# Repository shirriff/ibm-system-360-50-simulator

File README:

Microcode in 2050_vol18/19/20_Sep72.pdf

Volume 20 QZ_000_1 etc has mapping from address to e.g. QT100 page.

Microcode overview in Z22-2833-R_2050_Processing_Unit_Field_Engineering_Diagram_Manual_Jul66.pdf
Page 14 has instruction table

Warning: edit .ts files not .js!

Compile typescript with "tsc"

start web server:
python3 -m http.server

Open tests in browser, e.g. tests/instructions.html
Tests don't all pass currently

decode.js: generates the microcode expression box
disasm.js: disassembles a System/360 instruction
engine.js: the actual simulator engine
io.js: i/O simulation: very basic
sim.js: top-level simulator
utils.js: shared utility functions
viewer.js: used by display.html and viewer.html

display.html: displays microcode
sim.html: main simulator
viewer.html: search/diff

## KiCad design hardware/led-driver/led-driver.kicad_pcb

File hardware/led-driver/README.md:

This is a driver board for the Model 50 console lights (under development).
This board has 18 LEDs, matching the two-byte display segment on the console.
It would take 15 boards for the whole console, which has approximately 271 LEDs.
I'm planning to use yellow/orange 590nm LEDs which is what the [IBM 1620 Jr](https://github.com/IBM-1620/Junior) project used after a bunch of testing to see what matched the bulbs most closely.

The board uses [PCA9634](https://www.nxp.com/docs/en/data-sheet/PCA9634.pdf) LED I2C PWM driver chips.
Each chip drives 8 LEDs, so each board has three chips. The extra 6 LED outputs are wired and can be connected to other console LEDs.
This supports the irregular console lights that don't fit into groups of 18.

The LED chips have I2C addresses *001bbbb*,
*011bbbb*, and *101bbbb* where *bbbb* are the board bits from the solder jumpers. The first two bits select the chip on the board (0, 1, 2).
The first chip handles the low-order byte, the second chip handles the high-order byte, and the third chip handles the two parity lights.

The board has some optional functionality that can be installed as needed.

A [PCA9555](https://www.nxp.com/docs/en/data-sheet/PCA9555.pdf) 16-bit GPIO can read 16 switches from the console.
Its I2C address is *0100bbb*.

A [MCP47CVB01](https://ww1.microchip.com/downloads/en/DeviceDoc/MCP47CXBXX-Data-Sheet-DS20006089B.pdf) DAC chip provides a current to drive the console meter. Its I2C address is *10010bb*.

Two [ADS7828EB](https://www.ti.com/lit/gpn/ads7828) provide 8-channel analog-to-digital conversion.
This can read the console potentiometers.
The I2C addresses are *100100b* and *100101b*, using a single board bit. The second-last bit selects the chip on the board.

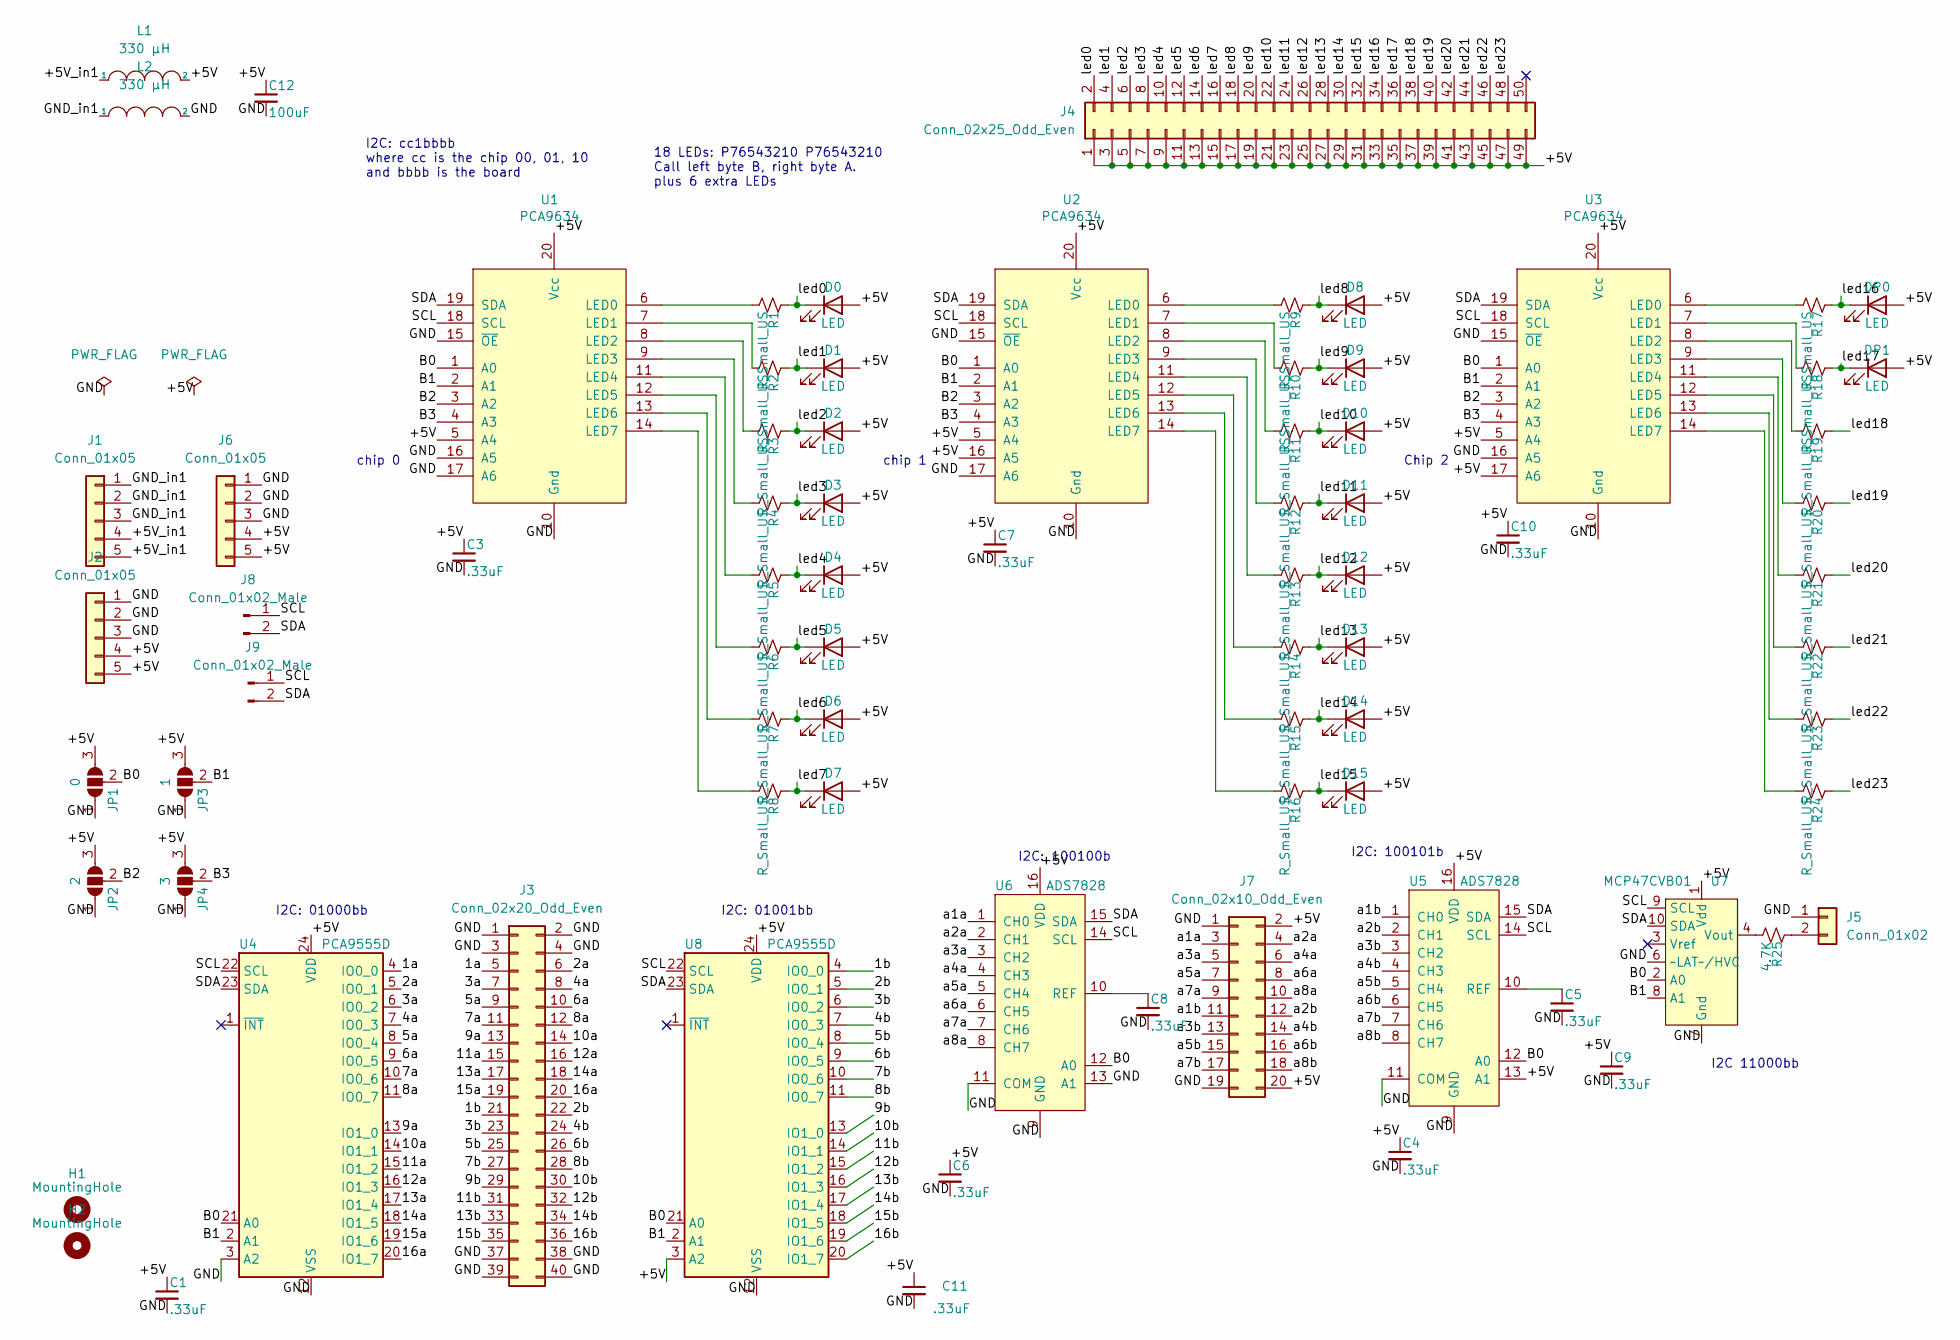
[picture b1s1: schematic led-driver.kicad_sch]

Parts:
C1, C3, C4, C5, C6, C7, C8, C9, C10, C11: .33uF; C_0805_2012Metric_Pad1.18x1.45mm_HandSolder
C12: 100uF; CP_EIA-7343-40_Kemet-Y_Pad2.25x2.55mm_HandSolder
D0, D1, D2, D3, D4, D5, D6, D7, D8, D9, D10, D11, D12, D13, D14, D15: LED; LED_D3.0mm-nosilk
DP0, DP1: LED; LED_D3.0mm-nosilk
H1, H2: MountingHole; MountingHole_3.7mm
J1, J2, J6: Conn_01x05; SAMTEC_TSS-105-04-F-S-RA
J3: Conn_02x20_Odd_Even; SAMTEC_TSS-120-04-F-D-RA-mirror
J4: Conn_02x25_Odd_Even; SAMTEC_TSS-125-04-F-D-RA-mirror
J5: Conn_01x02; SAMTEC_TSS-102-04-F-S-RA
J7: Conn_02x10_Odd_Even; SAMTEC_TSS-110-04-F-D-RA-mirror
J8, J9: Conn_01x02_Male; SAMTEC_TSS-102-04-F-S-RA
JP1: 0; SolderJumper-3_P1.3mm_Open_RoundedPad1.0x1.5mm_NumberLabels
JP2: 2; SolderJumper-3_P1.3mm_Open_RoundedPad1.0x1.5mm_NumberLabels
JP3: 1; SolderJumper-3_P1.3mm_Open_RoundedPad1.0x1.5mm_NumberLabels
JP4: 3; SolderJumper-3_P1.3mm_Open_RoundedPad1.0x1.5mm_NumberLabels
L1, L2: 330 µH; L_Bourns_SDR1307
R1, R2, R3, R4, R5, R6, R7, R8, R9, R10, R11, R12, R13, R14, R15, R16, R17, R18, R19, R20, R21, R22, R23, R24: R_Small_US; R_0805_2012Metric_Pad1.20x1.40mm_HandSolder
R25: 4.7K; R_0805_2012Metric_Pad1.20x1.40mm_HandSolder
U1, U2, U3: PCA9634; SOIC-20W_7.5x12.8mm_P1.27mm
U4, U8: PCA9555D; SOIC-24W_7.5x15.4mm_P1.27mm
U5, U6: ADS7828; TSSOP-16_4.4x5mm_P0.65mm
U7: MCP47CVB01; MSOP-10_3x3mm_P0.5mm

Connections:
/1a: J3.5, U4.4 (IO0_0)
/1b: J3.21, U8.4 (IO0_0)
/2a: J3.6, U4.5 (IO0_1)
/2b: J3.22, U8.5 (IO0_1)
/3a: J3.7, U4.6 (IO0_2)
/3b: J3.23, U8.6 (IO0_2)
/4a: J3.8, U4.7 (IO0_3)
/4b: J3.24, U8.7 (IO0_3)
/5a: J3.9, U4.8 (IO0_4)
/5b: J3.25, U8.8 (IO0_4)
/6a: J3.10, U4.9 (IO0_5)
/6b: J3.26, U8.9 (IO0_5)
/7a: J3.11, U4.10 (IO0_6)
/7b: J3.27, U8.10 (IO0_6)
/8a: J3.12, U4.11 (IO0_7)
/8b: J3.28, U8.11 (IO0_7)
/9a: J3.13, U4.13 (IO1_0)
/9b: J3.29, U8.13 (IO1_0)
/10a: J3.14, U4.14 (IO1_1)
/10b: J3.30, U8.14 (IO1_1)
/11a: J3.15, U4.15 (IO1_2)
/11b: J3.31, U8.15 (IO1_2)
/12a: J3.16, U4.16 (IO1_3)
/12b: J3.32, U8.16 (IO1_3)
/13a: J3.17, U4.17 (IO1_4)
/13b: J3.33, U8.17 (IO1_4)
/14a: J3.18, U4.18 (IO1_5)
/14b: J3.34, U8.18 (IO1_5)
/15a: J3.19, U4.19 (IO1_6)
/15b: J3.35, U8.19 (IO1_6)
/16a: J3.20, U4.20 (IO1_7)
/16b: J3.36, U8.20 (IO1_7)
/+5V: C1.1, C3.1, C4.1, C6.1, C7.1, C9.1, C10.1, C11.1, C12.1, D0.2 (A), D1.2 (A), D2.2 (A), D3.2 (A), D4.2 (A), D5.2 (A), D6.2 (A), D7.2 (A), D8.2 (A), D9.2 (A), D10.2 (A), D11.2 (A), D12.2 (A), D13.2 (A), D14.2 (A), D15.2 (A), DP0.2 (A), DP1.2 (A), J2.4, J2.5, J4.1, J4.3, J4.5, J4.7, J4.9, J4.11, J4.13, J4.15, J4.17, J4.19, J4.21, J4.23, J4.25, J4.27, J4.29, J4.31, J4.33, J4.35, J4.37, J4.39, J4.41, J4.43, J4.45, J4.47, J4.49, J6.4, J6.5, J7.2, J7.20, JP1.3 (B), JP2.3 (B), JP3.3 (B), JP4.3 (B), L1.2, U1.5 (A4), U1.20 (Vcc), U2.5 (A4), U2.16 (A5), U2.20 (Vcc), U3.5 (A4), U3.17 (A6), U3.20 (Vcc), U4.24 (VDD), U5.13 (A1), U5.16 (VDD), U6.16 (VDD), U7.1 (Vdd), U8.3 (A2), U8.24 (VDD)
/+5V_in1: J1.4, J1.5, L1.1
/B0: JP1.2 (C), U1.1 (A0), U2.1 (A0), U3.1 (A0), U4.21 (A0), U5.12 (A0), U6.12 (A0), U7.2 (A0), U8.21 (A0)
/B1: JP3.2 (C), U1.2 (A1), U2.2 (A1), U3.2 (A1), U4.2 (A1), U7.8 (A1), U8.2 (A1)
/B2: JP2.2 (C), U1.3 (A2), U2.3 (A2), U3.3 (A2)
/B3: JP4.2 (C), U1.4 (A3), U2.4 (A3), U3.4 (A3)
/GND: C1.2, C3.2, C4.2, C5.2, C6.2, C7.2, C8.2, C9.2, C10.2, C11.2, C12.2, J2.1, J2.2, J2.3, J3.1, J3.2, J3.3, J3.4, J3.37, J3.38, J3.39, J3.40, J5.1, J6.1, J6.2, J6.3, J7.1, J7.19, JP1.1 (A), JP2.1 (A), JP3.1 (A), JP4.1 (A), L2.2, U1.10 (Gnd), U1.15 (~OE), U1.16 (A5), U1.17 (A6), U2.10 (Gnd), U2.15 (~OE), U2.17 (A6), U3.10 (Gnd), U3.15 (~OE), U3.16 (A5), U4.3 (A2), U4.12 (VSS), U5.9 (GND), U5.11 (COM), U6.9 (GND), U6.11 (COM), U6.13 (A1), U7.6 (~LAT~/HVC), U7.7 (Gnd), U8.12 (VSS)
/GND_in1: J1.1, J1.2, J1.3, L2.1
/SCL: J8.1, J9.1, U1.18 (SCL), U2.18 (SCL), U3.18 (SCL), U4.22 (SCL), U5.14 (SCL), U6.14 (SCL), U7.9 (SCL), U8.22 (SCL)
/SDA: J8.2, J9.2, U1.19 (SDA), U2.19 (SDA), U3.19 (SDA), U4.23 (SDA), U5.15 (SDA), U6.15 (SDA), U7.10 (SDA), U8.23 (SDA)
/a1a: J7.3, U6.1 (CH0)
/a1b: J7.11, U5.1 (CH0)
/a2a: J7.4, U6.2 (CH1)
/a2b: J7.12, U5.2 (CH1)
/a3a: J7.5, U6.3 (CH2)
/a3b: J7.13, U5.3 (CH2)
/a4a: J7.6, U6.4 (CH3)
/a4b: J7.14, U5.4 (CH3)
/a5a: J7.7, U6.5 (CH4)
/a5b: J7.15, U5.5 (CH4)
/a6a: J7.8, U6.6 (CH5)
/a6b: J7.16, U5.6 (CH5)
/a7a: J7.9, U6.7 (CH6)
/a7b: J7.17, U5.7 (CH6)
/a8a: J7.10, U6.8 (CH7)
/a8b: J7.18, U5.8 (CH7)
/led0: D0.1 (K), J4.2, R1.1
/led1: D1.1 (K), J4.4, R2.1
/led2: D2.1 (K), J4.6, R3.1
/led3: D3.1 (K), J4.8, R4.1
/led4: D4.1 (K), J4.10, R5.1
/led5: D5.1 (K), J4.12, R6.1
/led6: D6.1 (K), J4.14, R7.1
/led7: D7.1 (K), J4.16, R8.1
/led8: D8.1 (K), J4.18, R9.1
/led9: D9.1 (K), J4.20, R10.1
/led10: D10.1 (K), J4.22, R11.1
/led11: D11.1 (K), J4.24, R12.1
/led12: D12.1 (K), J4.26, R13.1
/led13: D13.1 (K), J4.28, R14.1
/led14: D14.1 (K), J4.30, R15.1
/led15: D15.1 (K), J4.32, R16.1
/led16: DP0.1 (K), J4.34, R17.1
/led17: DP1.1 (K), J4.36, R18.1
/led18: J4.38, R19.1
/led19: J4.40, R20.1
/led20: J4.42, R21.1
/led21: J4.44, R22.1
/led22: J4.46, R23.1
/led23: J4.48, R24.1
unnamed: C5.1, U5.10 (REF)
unnamed: C8.1, U6.10 (REF)
unnamed: J5.2, R25.1
unnamed: R1.2, U1.6 (LED0)
unnamed: R2.2, U1.7 (LED1)
unnamed: R3.2, U1.8 (LED2)
unnamed: R4.2, U1.9 (LED3)
unnamed: R5.2, U1.11 (LED4)
unnamed: R6.2, U1.12 (LED5)
unnamed: R7.2, U1.13 (LED6)
unnamed: R8.2, U1.14 (LED7)
unnamed: R9.2, U2.6 (LED0)
unnamed: R10.2, U2.7 (LED1)
unnamed: R11.2, U2.8 (LED2)
unnamed: R12.2, U2.9 (LED3)
unnamed: R13.2, U2.11 (LED4)
unnamed: R14.2, U2.12 (LED5)
unnamed: R15.2, U2.13 (LED6)
unnamed: R16.2, U2.14 (LED7)
unnamed: R17.2, U3.6 (LED0)
unnamed: R18.2, U3.7 (LED1)
unnamed: R19.2, U3.8 (LED2)
unnamed: R20.2, U3.9 (LED3)
unnamed: R21.2, U3.11 (LED4)
unnamed: R22.2, U3.12 (LED5)
unnamed: R23.2, U3.13 (LED6)
unnamed: R24.2, U3.14 (LED7)
unnamed: R25.2, U7.4 (Vout)

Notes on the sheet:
I2C: 100101b
chip 1
I2C 11000bb
I2C: cc1bbbb where cc is the chip 00, 01, 10 and bbbb is the board
Chip 2
chip 0
18 LEDs: P76543210 P76543210 Call left byte B, right byte A. plus 6 extra LEDs
I2C: 01000bb
I2C: 100100b
I2C: 01001bb

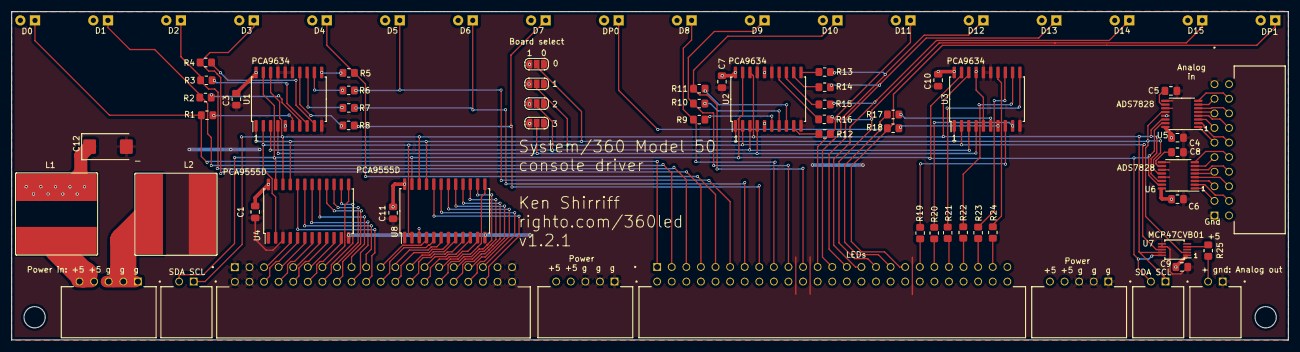
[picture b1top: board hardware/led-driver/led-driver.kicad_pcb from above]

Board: 2 copper layers, 222.2 x 57.1 mm, 79 parts (0 on the bottom side), 110 nets.

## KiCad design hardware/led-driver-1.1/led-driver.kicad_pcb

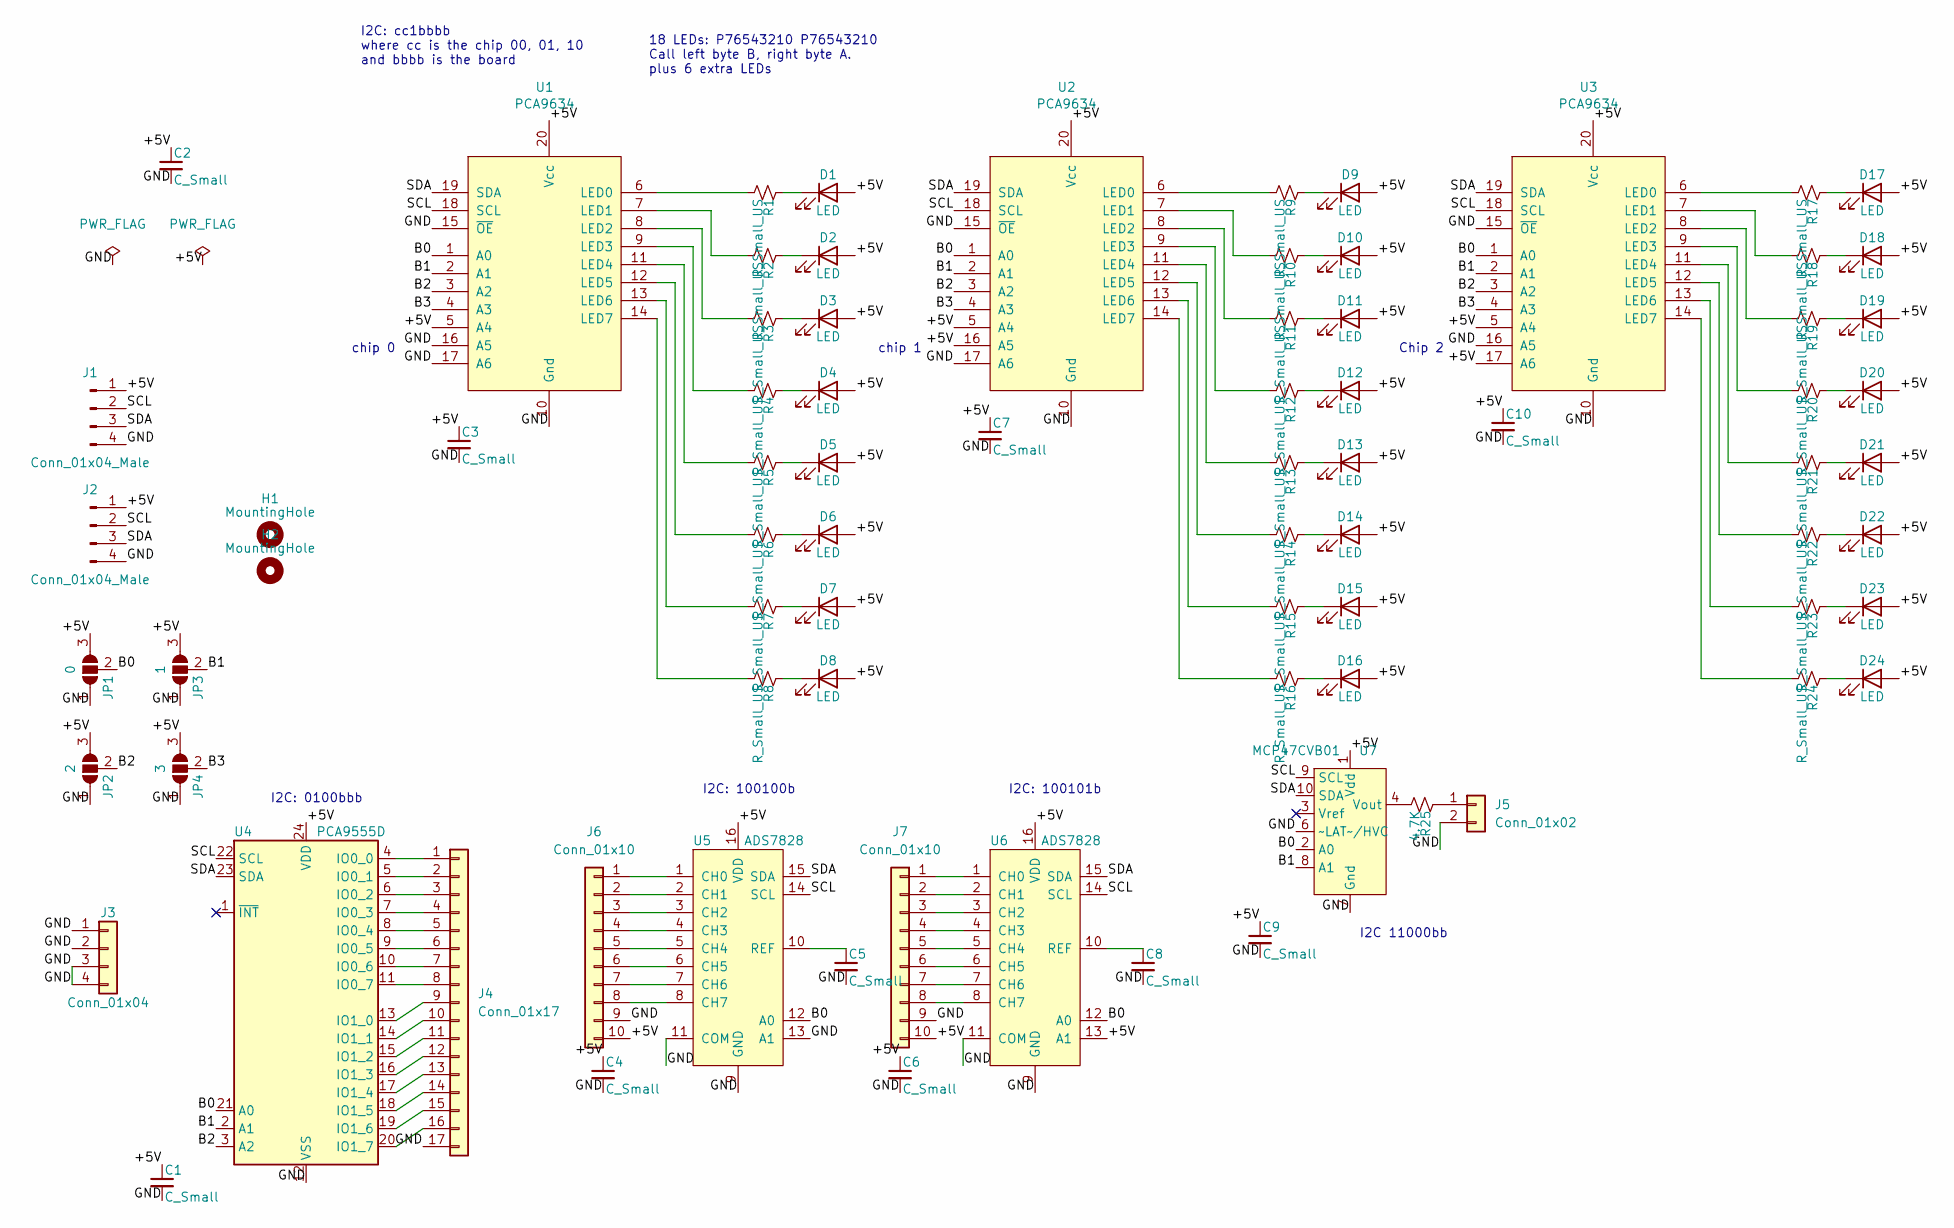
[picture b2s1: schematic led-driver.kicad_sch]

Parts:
C1, C2, C3, C4, C5, C6, C7, C8, C9, C10: C_Small; C_0805_2012Metric_Pad1.18x1.45mm_HandSolder
D1, D2, D3, D4, D5, D6, D7, D8, D9, D10, D11, D12, D13, D14, D15, D16, D17, D18: LED; LED_D3.0mm-nosilk
D19, D20, D21, D22, D23, D24: LED; PinHeader_1x02_P2.54mm_Vertical
H1, H2: MountingHole; MountingHole_3.7mm
J1, J2: Conn_01x04_Male; PinHeader_1x04_P2.54mm_Vertical_mirrored
J3: Conn_01x04; PinSocket_1x04_P2.54mm_Vertical
J4: Conn_01x17; PinSocket_1x17_P2.54mm_Vertical
J5: Conn_01x02; PinHeader_1x02_P2.54mm_Vertical
J6, J7: Conn_01x10; PinHeader_1x10_P2.54mm_Vertical
JP1: 0; SolderJumper-3_P1.3mm_Open_RoundedPad1.0x1.5mm_NumberLabels
JP2: 2; SolderJumper-3_P1.3mm_Open_RoundedPad1.0x1.5mm_NumberLabels
JP3: 1; SolderJumper-3_P1.3mm_Open_RoundedPad1.0x1.5mm_NumberLabels
JP4: 3; SolderJumper-3_P1.3mm_Open_RoundedPad1.0x1.5mm_NumberLabels
R1, R2, R3, R4, R5, R6, R7, R8, R9, R10, R11, R12, R13, R14, R15, R16, R17, R18, R19, R20, R21, R22, R23, R24: R_Small_US; R_0805_2012Metric_Pad1.20x1.40mm_HandSolder
R25: 4.7K; R_0805_2012Metric_Pad1.20x1.40mm_HandSolder
U1, U2, U3: PCA9634; SOIC-20W_7.5x12.8mm_P1.27mm
U4: PCA9555D; SOIC-24W_7.5x15.4mm_P1.27mm
U5, U6: ADS7828; TSSOP-16_4.4x5mm_P0.65mm
U7: MCP47CVB01; MSOP-10_3x3mm_P0.5mm

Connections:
/+5V: C1.1, C2.1, C3.1, C4.1, C6.1, C7.1, C9.1, C10.1, D1.2 (A), D2.2 (A), D3.2 (A), D4.2 (A), D5.2 (A), D6.2 (A), D7.2 (A), D8.2 (A), D9.2 (A), D10.2 (A), D11.2 (A), D12.2 (A), D13.2 (A), D14.2 (A), D15.2 (A), D16.2 (A), D17.2 (A), D18.2 (A), D19.2 (A), D20.2 (A), D21.2 (A), D22.2 (A), D23.2 (A), D24.2 (A), J1.1, J2.1, J6.10, J7.10, JP1.3 (B), JP2.3 (B), JP3.3 (B), JP4.3 (B), U1.5 (A4), U1.20 (Vcc), U2.5 (A4), U2.16 (A5), U2.20 (Vcc), U3.5 (A4), U3.17 (A6), U3.20 (Vcc), U4.24 (VDD), U5.16 (VDD), U6.13 (A1), U6.16 (VDD), U7.1 (Vdd)
/B0: JP1.2 (C), U1.1 (A0), U2.1 (A0), U3.1 (A0), U4.21 (A0), U5.12 (A0), U6.12 (A0), U7.2 (A0)
/B1: JP3.2 (C), U1.2 (A1), U2.2 (A1), U3.2 (A1), U4.2 (A1), U7.8 (A1)
/B2: JP2.2 (C), U1.3 (A2), U2.3 (A2), U3.3 (A2), U4.3 (A2)
/B3: JP4.2 (C), U1.4 (A3), U2.4 (A3), U3.4 (A3)
/GND: C1.2, C2.2, C3.2, C4.2, C5.2, C6.2, C7.2, C8.2, C9.2, C10.2, J1.4, J2.4, J3.1, J3.2, J3.3, J3.4, J4.17, J5.2, J6.9, J7.9, JP1.1 (A), JP2.1 (A), JP3.1 (A), JP4.1 (A), U1.10 (Gnd), U1.15 (~OE), U1.16 (A5), U1.17 (A6), U2.10 (Gnd), U2.15 (~OE), U2.17 (A6), U3.10 (Gnd), U3.15 (~OE), U3.16 (A5), U4.12 (VSS), U5.9 (GND), U5.11 (COM), U5.13 (A1), U6.9 (GND), U6.11 (COM), U7.6 (~LAT~/HVC), U7.7 (Gnd)
/SCL: J1.2, J2.2, U1.18 (SCL), U2.18 (SCL), U3.18 (SCL), U4.22 (SCL), U5.14 (SCL), U6.14 (SCL), U7.9 (SCL)
/SDA: J1.3, J2.3, U1.19 (SDA), U2.19 (SDA), U3.19 (SDA), U4.23 (SDA), U5.15 (SDA), U6.15 (SDA), U7.10 (SDA)
unnamed: C5.1, U5.10 (REF)
unnamed: C8.1, U6.10 (REF)
unnamed: D1.1 (K), R1.1
unnamed: D2.1 (K), R2.1
unnamed: D3.1 (K), R3.1
unnamed: D4.1 (K), R4.1
unnamed: D5.1 (K), R5.1
unnamed: D6.1 (K), R6.1
unnamed: D7.1 (K), R7.1
unnamed: D8.1 (K), R8.1
unnamed: D9.1 (K), R9.1
unnamed: D10.1 (K), R10.1
unnamed: D11.1 (K), R11.1
unnamed: D12.1 (K), R12.1
unnamed: D13.1 (K), R13.1
unnamed: D14.1 (K), R14.1
unnamed: D15.1 (K), R15.1
unnamed: D16.1 (K), R16.1
unnamed: D17.1 (K), R17.1
unnamed: D18.1 (K), R18.1
unnamed: D19.1 (K), R19.1
unnamed: D20.1 (K), R20.1
unnamed: D21.1 (K), R21.1
unnamed: D22.1 (K), R22.1
unnamed: D23.1 (K), R23.1
unnamed: D24.1 (K), R24.1
unnamed: J5.1, R25.1
unnamed: J6.1, U5.1 (CH0)
unnamed: J6.2, U5.2 (CH1)
unnamed: J6.3, U5.3 (CH2)
unnamed: J6.4, U5.4 (CH3)
unnamed: J6.5, U5.5 (CH4)
unnamed: J6.6, U5.6 (CH5)
unnamed: J6.7, U5.7 (CH6)
unnamed: J6.8, U5.8 (CH7)
unnamed: R1.2, U1.6 (LED0)
unnamed: R2.2, U1.7 (LED1)
unnamed: R3.2, U1.8 (LED2)
unnamed: R4.2, U1.9 (LED3)
unnamed: R5.2, U1.11 (LED4)
unnamed: R6.2, U1.12 (LED5)
unnamed: R7.2, U1.13 (LED6)
unnamed: R8.2, U1.14 (LED7)
unnamed: R9.2, U2.6 (LED0)
unnamed: R10.2, U2.7 (LED1)
unnamed: R11.2, U2.8 (LED2)
unnamed: R12.2, U2.9 (LED3)
unnamed: R13.2, U2.11 (LED4)
unnamed: R14.2, U2.12 (LED5)
unnamed: R15.2, U2.13 (LED6)
unnamed: R16.2, U2.14 (LED7)
unnamed: R17.2, U3.6 (LED0)
unnamed: R18.2, U3.7 (LED1)
unnamed: R19.2, U3.8 (LED2)
unnamed: R20.2, U3.9 (LED3)
unnamed: R21.2, U3.11 (LED4)
unnamed: R22.2, U3.12 (LED5)
unnamed: R23.2, U3.13 (LED6)
unnamed: R24.2, U3.14 (LED7)
unnamed: R25.2, U7.4 (Vout)
unnamed: J4.1, U4.4 (IO0_0)
unnamed: J4.2, U4.5 (IO0_1)
unnamed: J4.3, U4.6 (IO0_2)
unnamed: J4.4, U4.7 (IO0_3)
unnamed: J4.5, U4.8 (IO0_4)
unnamed: J4.6, U4.9 (IO0_5)
unnamed: J4.7, U4.10 (IO0_6)
unnamed: J4.8, U4.11 (IO0_7)
unnamed: J4.9, U4.13 (IO1_0)
unnamed: J4.10, U4.14 (IO1_1)
unnamed: J4.11, U4.15 (IO1_2)
unnamed: J4.12, U4.16 (IO1_3)
unnamed: J4.13, U4.17 (IO1_4)
unnamed: J4.14, U4.18 (IO1_5)
unnamed: J4.15, U4.19 (IO1_6)
unnamed: J4.16, U4.20 (IO1_7)
unnamed: J7.1, U6.1 (CH0)
unnamed: J7.2, U6.2 (CH1)
unnamed: J7.3, U6.3 (CH2)
unnamed: J7.4, U6.4 (CH3)
unnamed: J7.5, U6.5 (CH4)
unnamed: J7.6, U6.6 (CH5)
unnamed: J7.7, U6.7 (CH6)
unnamed: J7.8, U6.8 (CH7)

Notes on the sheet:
chip 1
I2C: 100101b
I2C 11000bb
I2C: cc1bbbb where cc is the chip 00, 01, 10 and bbbb is the board
Chip 2
chip 0
18 LEDs: P76543210 P76543210 Call left byte B, right byte A. plus 6 extra LEDs
I2C: 0100bbb
I2C: 100100b

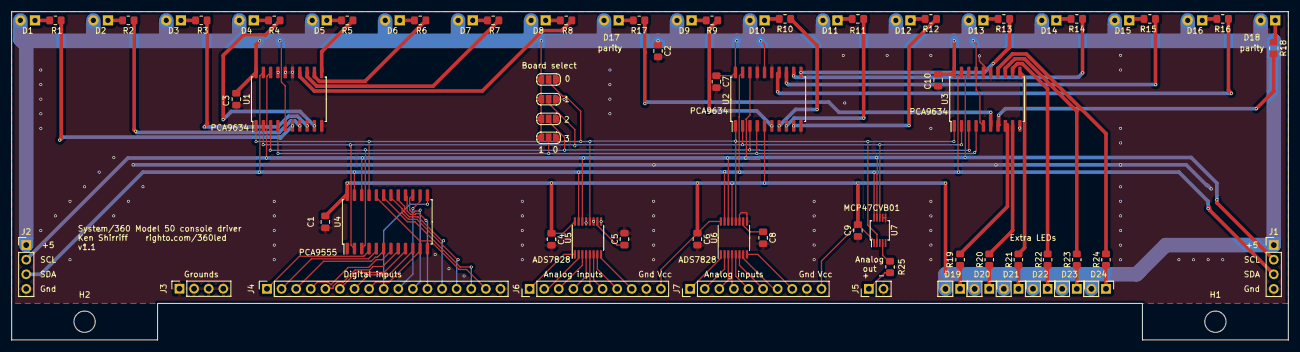
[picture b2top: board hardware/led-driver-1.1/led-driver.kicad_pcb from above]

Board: 2 copper layers, 222.2 x 57.1 mm, 79 parts (0 on the bottom side), 92 nets.

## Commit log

2019-03-19 Microcode analysis programs.
2019-03-21 Improvements. Refactor, splitting out decode.js
2019-03-21 Add initial simulator code.
2019-03-22 Add simulation engine.
2019-03-22 Simulator improvements.
2019-03-23 More improvements. Runs part of IPL.
2019-03-24 More improvements. Mem display.
2019-03-25 Basic I/O, more microinstructions. Now will IPL and fetch instruction.
2019-03-25 Fix PSW handling (split out CC, IA, IC). Add some (not-passing) tests for other functions.
2019-03-26 Now does an addition.
2019-03-26 Fixed local storage update. Now add works.
2019-03-26 Disassemble instruction
2019-03-28 Add unittests for instructions (mostly failing).
2019-03-28 More engine implementation.
2019-03-28 Clean up indentation.
2019-03-31 Lots of fixes.
2019-03-31 More fixes
2019-04-01 Mark failing tests as "skip" in preparation for refactor.
2019-04-01 Refactor: split adder and roar code into multiple routines to simplify testing.
2019-04-01 Clean up tests
2019-04-02 Lots more unittests for micro-instructions.
2019-04-02 Add 'pending' to do stores at end.
2019-04-02 Split storage out of mover.
2019-04-02 Split PSW into individual fields.
2019-04-02 PSW fixes. Set overflow mask correctly.
2019-04-03 Fixes, cleanup for shifts.
2019-04-03 Fix multiplication
2019-04-03 Fix shift left. Put mover before AL to access F before it is modified by shift.
2019-04-04 Change CC to CR. Fix branch.
2019-04-04 Fix comment.
2019-04-04 Refactored localStorage routines, added new code, tests.
2019-04-04 Fix LS→L,R→LS
2019-04-04 Fix conditions to check old vs new T as appropriate. This fixes division.
2019-04-05 Fix timing of T updates. T0 is the state before the adder latch, T is the state afterwards. Merge storePending with adderLatch
2019-04-07 Check in the OCR'd data.
2019-04-07 Fixes to data2.txt
2019-04-07 Fix microcode errors
2019-04-09 Switch to TypeScript. Compile with 'tsc'.
2019-04-09 Fix Load Multiple. (Also microcode fix.)
2019-04-09 Get CVB convert binary working.
2019-04-09 Clean up files
2019-04-09 Updated microcode data.
2019-04-09 Cleanup
2019-04-09 Refactor mover
2019-04-09 Refactor mover. Fix PSW4. Add tests.
2019-04-09 Fix branch and link, branch on count tests.
2019-04-10 Changed B0. Not convinced it's looking at the right half-word, but the compare functions work now. Also changed G1, G2 to not go below 0.
2019-04-10 Clean up carries, implement MVC.
2019-04-10 Fix MVC test.
2019-04-11 Fix SSK, ISK. Implement KEY→F, F→KEY, PROB.
2019-04-11 Implement Test and Set. Implement D→CR*BS
2019-04-11 Get floating point LCER working. Implement ¬S4,S4→CR, S4,¬S4→CR, 1→REFETCH
2019-04-11 Add stubs for remaining instructions.
2019-04-12 Floating point fixes, fixed T13=0
2019-04-12 Add more test stubs
2019-04-12 Get immediate operations working. Big problem with SETCRLOG, masking addition seems like a hack, but needed to make CLI work. Fix negative values. Cleaned up BS mask generation.
2019-04-12 Get LPSW working.
2019-04-12 Fix IAR: 24 bits.
2019-04-12 Branch and link test
2019-04-12 Fix off-by-1 in SS instruction disassembly.
2019-04-18 Fix decimal correction, implement IVD/RSGNS.
2019-04-18 Fix handling of pending, especially BS, to fix decimal ops.
2019-04-19 Floating point halve implemented. Also BC1B, FPSL4, F→FPSL4, FPSR4→F, 1→FPSR4→F, E→FPSL4, R13, L13, FPZERO.
2019-04-19 Add FPZERO test, fix Q→SR1→F test.
2019-04-19 More tests
2019-04-19 More instruction tests.
2019-04-19 Add more tests. Fix WS handling: working storage is 1x not 3x.
2019-04-19 Change length field to decimal for consistency.
2019-04-19 Fix ZAP tests. Add EDIT test that isn't working yet.
2019-04-20 More tests, some pass. Implement LWA to get MVO working.
2019-04-20 Implement MD=FP
2019-04-20 Add lots more tests, random floating point tests. Many test currently fail.
2019-04-20 Wrote more tests: 1045 pass, 61 fail. No more skipped.
2019-04-20 Implement (T=0)→S3
2019-04-20 Implement ED*FP and F→ROAR
2019-04-20 Add more to FPZERO, implement L0,¬S4→ and L0,S4→.
2019-04-21 Fix →J. Implement hypothesized FPZERO,E→FN, CANG. Stub CHLOG.
2019-04-22 Fix BC1B, FPSL4
2019-04-28 Fixes to engine tests, from C++ version.
2019-04-28 Engine fixes.
2019-04-28 C++ version in Xcode
2019-04-28 Tests in Xcode
2019-04-28 C++ version of disasm and engine
2019-04-29 Rename disasm.cpp, engine.cpp, fix some tests.
2019-05-10 Fix a bunch of decoder tests to match current state of decoder
2021-10-14 Permission changes
2021-10-14 C++ version
2021-10-14 Misc changes, checkpoint of code before writing more.
2021-10-14 Migrate pyserver to python3
2021-10-17 UI test files
2021-10-18 Canvas handling kind of working
2021-10-18 Some cleanup
2021-10-18 Checkpoint.
2021-10-19 Add regions and light positions.
2021-10-20 Checkpoint of code.
2021-10-20 Factor out JS code from index.html to ui.js.
2021-10-20 Cleanup.
2021-10-20 Resize not working.
2021-10-20 Support roller updates.
2021-10-20 Migrate UI test files to main directory.
2021-10-20 Fix tsc issues.
2021-10-21 Merging with old code.
2021-10-21 Refactoring, more UI support.
2021-10-22 Add some light support, unittest.
2021-10-22 Fix initialization.
2021-10-22 Check in OCR data.
2021-10-22 Console light changes
2021-10-22 Get basic lights working.
2021-10-22 Update OCR parser to include raw bits
2021-10-24 Support multi-color lights. Use high-res console image.
2021-10-29 Make dial adjustable.
2021-12-22 Create README.md for Github
2021-12-22 Misc files.
2021-12-22 Fix test paths.
2021-12-24 Add documentation strings on the microcode actions.
2022-01-01 Lots of refactoring. Use Promises to make sure the images and data are loaded before running. Try to clean up the canvas scaling.
2022-01-01 First cut at adding a description to the micro-instruction.
2022-01-01 Fix image display. Image displays correctly, but lights are wrong. Still need to scale canvas to double resolution.
2022-01-01 Fix double-resolution canvas handling
2022-01-01 Change coordinate system so (0,0) is in center of screen. Drawing routines use a coordinate system based on the console image with (0,0) in upper left.
2022-01-02 Add panning limits
2022-01-02 Fix mover description.
2022-01-02 Fix lamp test
2022-01-02 Add micro-instruction popup.
2022-01-02 Add functions for power on, power off, epo.
2022-01-02 Add more Typescript types.
2022-01-04 Check in the images.
2022-01-04 Improved light support, including power on light.
2022-01-05 Add a sample program in code.ts (Not working yet.)
2022-01-05 Add the microcode data.
2022-01-05 Add ALD page descriptions to microcode.
2022-01-06 Fix resize when shrinking window
2022-01-06 Fix canvas sizing and resizing. Hopefully it now works correctly.
2022-01-06 Add highlighting on LSAR reads/writes.
2022-01-06 Sidebar improvements. Register tooltips, microcode addr tooltip. Cleaned up side cards. Changed LS to 16 columns. Initialized registers to 0.
2022-01-06 Add missing arrows in microcode blocks. Fix tests to work with current code.
2022-01-07 Fix parity calculation and test.
2022-01-07 Fix initialization so tests work cleanly.
2022-01-07 Fix some descriptions.
2022-01-07 Fix the sample machine code.
2022-01-07 Clean up memory display.
2022-01-07 Make addresses 3 bytes. Add logging of microcode for debugging.
2022-01-07 Remove unused register display.
2022-01-07 Fix MHL instruction.
2022-01-07 Add local storage labels.
2022-01-07 Fix SAR tests: make 24 bits.
2022-01-08 Fix adder functions AD. Also get the unittests working for them. The functions now match the documented descriptions.
2022-01-08 Improve TR unittest.
2022-01-08 Fix IV micro-ops. Fix tests. Implement Invalid Address Stat (IAS)
2022-01-08 Add support for wait at end of program, resetting. Increase frame rate to 200ms.
2022-01-08 Refactor. Pull out displayMicroOp function
2022-01-09 Add memory viewer.
2022-01-09 Various fixes to the AL microcode operations and associated tests.
2022-01-10 Fix AB fields and tests.
2022-01-10 Enforce word alignment on core viewer.
2022-01-10 Update BB actions and tests.
2022-01-10 Fix some SS functions and tests.
2022-01-13 First attempt at SS 27: exponent difference implementation. The documentation for this is a bit sketchy. Tests not currently passing.
2022-01-13 Working on instruction testing. Improve debug logging.
2022-01-13 Check in test data (microcode/sheets/ald)
2022-01-14 Get floating point addition working. This mainly involved fixing the corner cases for the exponent difference S47,ED*FP. There appear to be a couple typos in the documentation for this. Also got the 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
2022-01-14 Finish SS micro-orders.
2022-01-14 Clean up function to test if floating point result is "close".
2022-01-14 Skip unimplemented tests.
2022-01-14 Fix IAS, DC0. Specifically, invalid address apparently should trigger when the 8K memory size is exceeded. A hot1 should override DC0's carry, in order for decimal add signs to be right.
2022-01-14 Fix privilege test
2022-01-15 Fix KEY tests
2022-01-15 Fix short multiplication by flipping sign in ED*FP. This seems backward compard to the documentation, but the documentation is a bit ambiguous. Multiplication now yields the right sign so it empirica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
2022-01-15 Fix G1, G2 counter handling.
2022-01-17 Fixed updates of S flags in adderT(). The problem is that these updates can't be applied until the end of the cycle. because other code needs the old values. So I put them into a 'pending' list to be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
2022-01-17 Fix timing of J register update. This fixes some long floating point multiplies.
2022-01-17 Fix SR4→H behavior. This fixes some multiplies.
2022-01-17 Fix a bunch of partially-implemented tests.
2022-01-18 Fix timing of G1/G2 updates by using 'pending'.
2022-01-18 Implement special case for W→MMB to fix table lookup. W→MMB(E?): clean up implementation, add tests.
2022-01-18 Fix CVD, translate tests.
2022-01-18 Fix edit stats. Fix edit tests.
2022-01-19 Add basic division test.
2022-01-19 Fix some division tests, add error checking.
2022-01-19 Fix multiply test.
2022-01-19 Fix lots of broken tests. (Mostly tests that were cut-and-pasted but not completed.)
2022-01-19 Fix ED*FP complementation handling. This function needs the uncomplemented input, so I added that to the state. Now the engine and instruction unittests pass.
2022-01-19 Fix decoder unittest. Now all tests pass.
2022-01-19 Improve restart of program
2022-01-19 Remove warning for unimplemented function while halting.
2022-01-19 Display instruction name.
2022-01-19 Add favicon
2022-01-21 Make display responsive. Display the sidebar underneath on a phone.
2022-01-21 Keep core memory viewer enabled.
2022-01-21 Fix stopping behavior on MANUAL→STOP
2022-01-21 Improve display on phone.
2022-01-21 Fix microcode box display. On Android, arrows aren't fixed width so the right hand edge of the box is ragged. Wrap the rest of the box in a fixed-width div so the right edge stays even.
2022-01-22 Put memory in 2 columns instead of 4.
2022-01-22 Get button clicks working on mobile. Needed to handle touchend as well as mouseup.
2022-01-22 Add a "Loading..." message.
2022-01-24 Remove beta, add blog link.
2022-01-24 Fix title alignment on narrow screens.
2022-02-01 LED driver board for Model 50 console. This board drives 18 LEDs (plus potentially 6 extras).
2022-02-01 Narrower board: remove explicit ground trace, use fill.
2022-02-01 Improve board, move to KiCad 6.
2022-02-01 Rendering of the board.
2022-02-01 Update README.md
    Explain chips and addressing.
2022-02-07 LED driver v1.1
2022-02-07 Add README
2022-02-07 Update board image.
2022-02-25 Update 1.1 schematic.
2022-02-25 I2C assignment program.
2022-04-06 Submitted version of board, 1.2.1
